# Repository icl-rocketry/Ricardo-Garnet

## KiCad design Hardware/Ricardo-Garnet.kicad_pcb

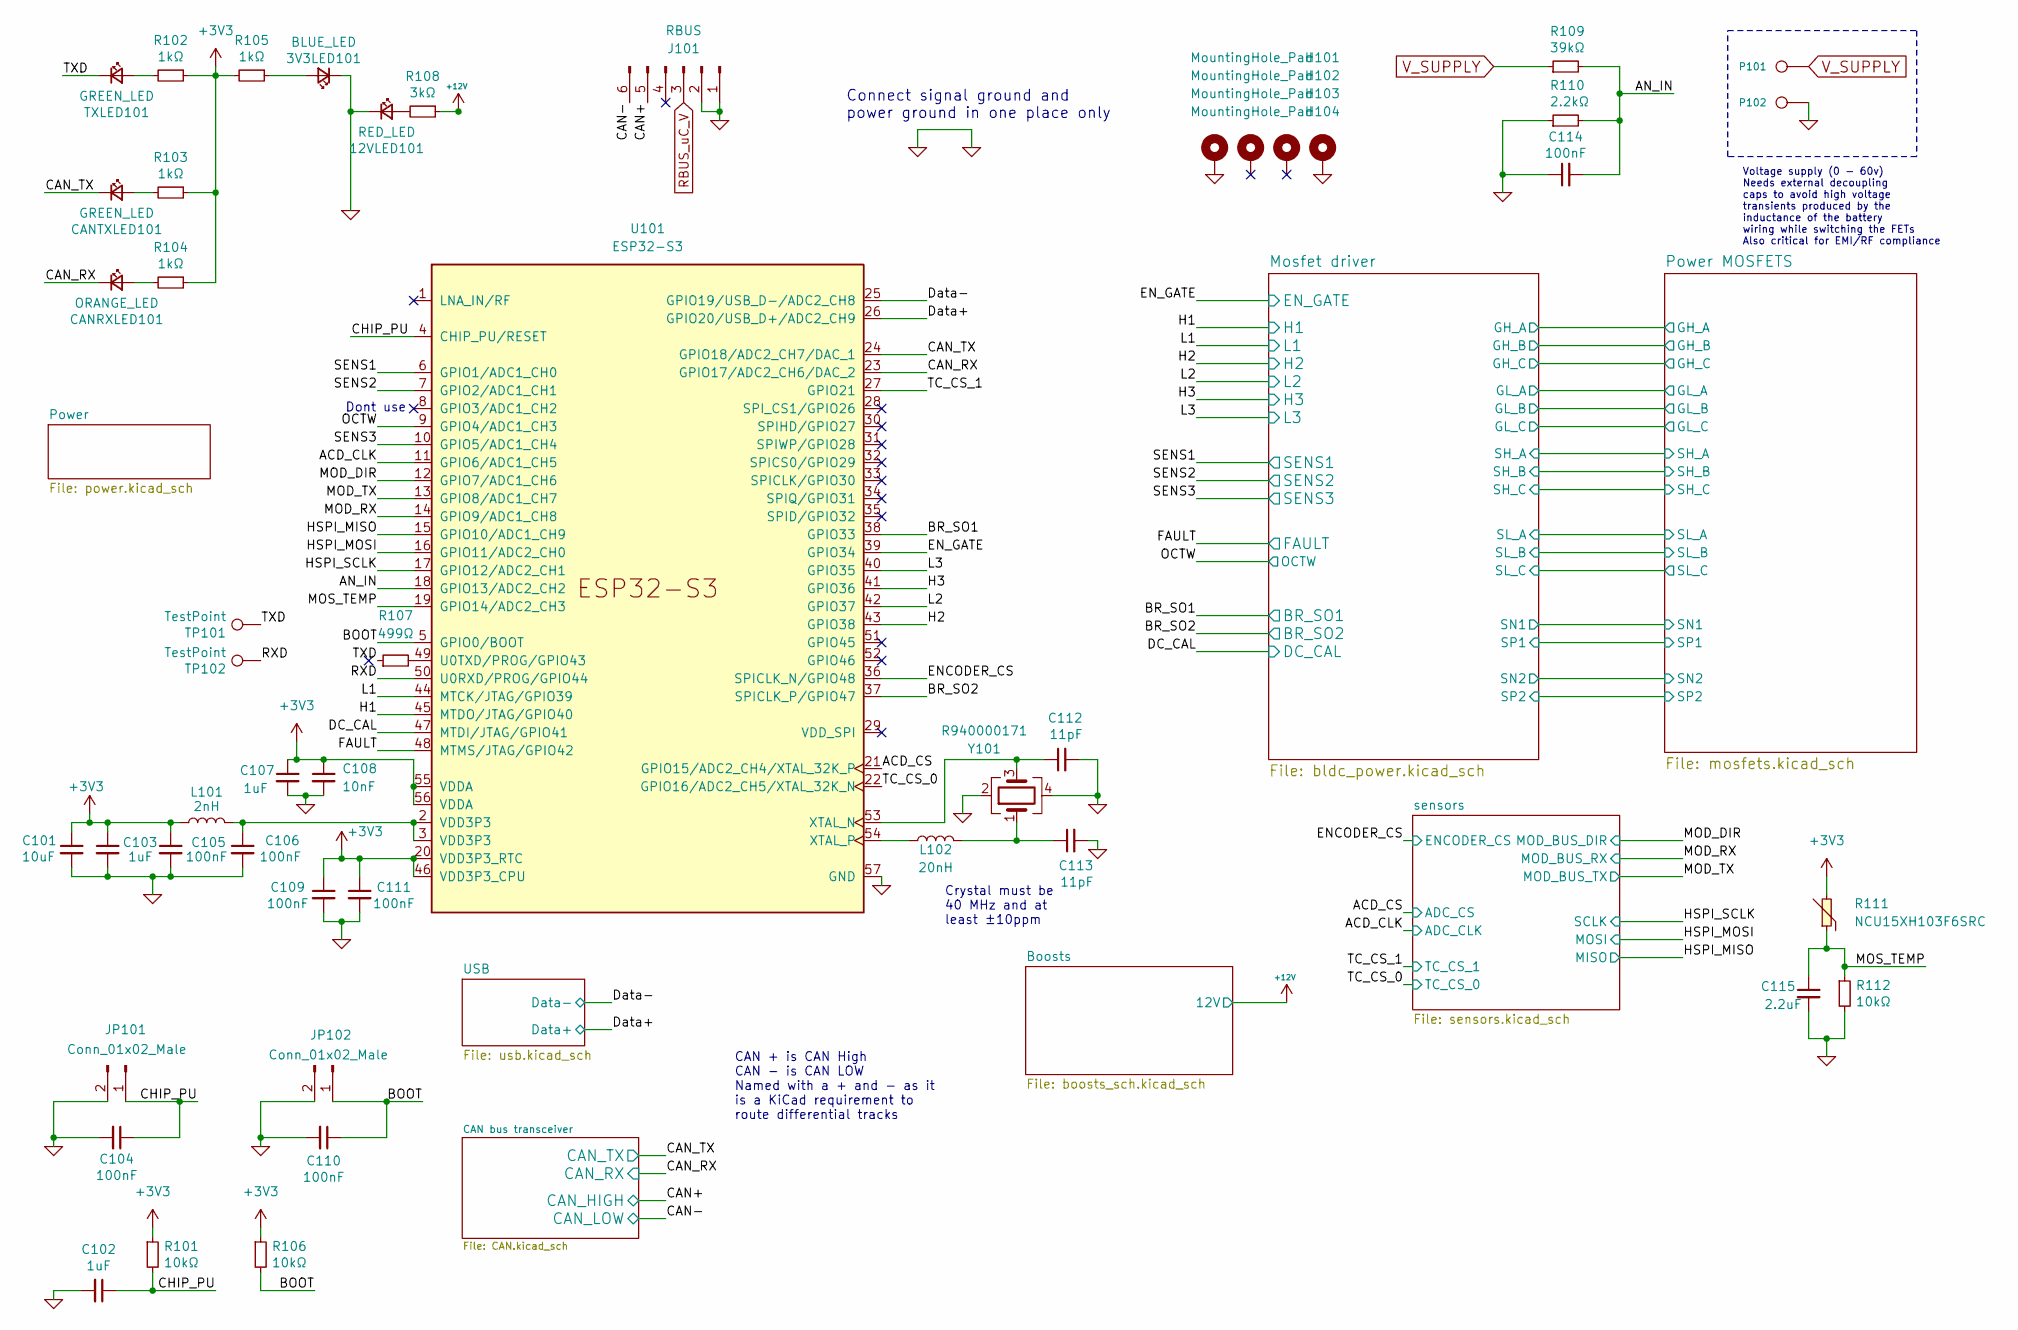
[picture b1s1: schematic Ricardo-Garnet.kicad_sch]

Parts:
3V3LED101: BLUE_LED; LED_0402_1005Metric
12VLED101: RED_LED; LED_0402_1005Metric
C101: 10uF; C_0603_1608Metric
C102, C103, C107: 1uF; C_0402_1005Metric
C104, C105, C106, C109, C110, C111, C114: 100nF; C_0402_1005Metric
C108: 10nF; C_0402_1005Metric
C112, C113: 11pF; C_0402_1005Metric
C115: 2.2uF; C_0402_1005Metric
CANRXLED101: ORANGE_LED; LED_0402_1005Metric
CANTXLED101: GREEN_LED; LED_0402_1005Metric
H101, H102, H103, H104: MountingHole_Pad; MountingHole_3.2mm_M3_DIN965_Pad
J101: RBUS; Molex_Mini-Fit_Jr_5569-06A2_2x03_P4.20mm_Horizontal
JP101, JP102: Conn_01x02_Male; PinHeader_1x02_P2.54mm_Vertical
L101: 2nH; L_0402_1005Metric
L102: 20nH; L_0402_1005Metric
P101: IN+; 1PAD_4x5mm
P102: IN-; 1PAD_4x5mm
R101, R106, R112: 10kΩ; R_0402_1005Metric
R102, R103, R104, R105: 1kΩ; R_0402_1005Metric
R107: 499Ω; R_0402_1005Metric
R108: 3kΩ; R_0402_1005Metric
R109: 39kΩ; R_0402_1005Metric
R110: 2.2kΩ; R_0402_1005Metric
R111: NCU15XH103F6SRC; R0402; MPN NCU15XH103F6SRC; LCSC Part C333993
TP101, TP102: TestPoint; TestPoint_Pad_D1.0mm
TXLED101: GREEN_LED; LED_0402_1005Metric
U101: ESP32-S3; QFN40P700X700X90-57N
Y101: R940000171; Crystal_SMD_2016-4Pin_2.0x1.6mm

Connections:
+3V3: C101.1, C103.1, C105.1, C107.1, C108.1, C109.1, C111.1, L101.1, R101.1, R102.1, R103.1, R104.1, R105.2, R106.1, R111.2, U101.20 (VDD3P3_RTC), U101.46 (VDD3P3_CPU), U101.55 (VDDA), U101.56 (VDDA); also elsewhere on the board
+12V: R108.1; also elsewhere on the board
/ACD_CLK: U101.11 (GPIO6/ADC1_CH5); also elsewhere on the board
/ACD_CS: U101.21 (GPIO15/ADC2_CH4/XTAL_32K_P); also elsewhere on the board
/AN_IN: C114.2, R109.2, R110.2, U101.18 (GPIO13/ADC2_CH2)
/BOOT: C110.1, JP102.1, R106.2, U101.5 (GPIO0/BOOT)
/BR_SO1: U101.38 (GPIO33); also elsewhere on the board
/BR_SO2: U101.37 (SPICLK_P/GPIO47); also elsewhere on the board
/CAN+: J101.5; also elsewhere on the board
/CAN-: J101.6; also elsewhere on the board
/CAN_RX: CANRXLED101.1 (K), U101.23 (GPIO17/ADC2_CH6/DAC_2); also elsewhere on the board
/CAN_TX: CANTXLED101.1 (K), U101.24 (GPIO18/ADC2_CH7/DAC_1); also elsewhere on the board
/CHIP_PU: C102.1, C104.1, JP101.1, R101.2, U101.4 (CHIP_PU/RESET)
/DC_CAL: U101.47 (MTDI/JTAG/GPIO41); also elsewhere on the board
/Data+: U101.26 (GPIO20/USB_D+/ADC2_CH9); also elsewhere on the board
/Data-: U101.25 (GPIO19/USB_D-/ADC2_CH8); also elsewhere on the board
/ENCODER_CS: U101.36 (SPICLK_N/GPIO48); also elsewhere on the board
/EN_GATE: U101.39 (GPIO34); also elsewhere on the board
/FAULT: U101.48 (MTMS/JTAG/GPIO42); also elsewhere on the board
/H1: U101.45 (MTDO/JTAG/GPIO40); also elsewhere on the board
/H2: U101.43 (GPIO38); also elsewhere on the board
/H3: U101.41 (GPIO36); also elsewhere on the board
/HSPI_MISO: U101.15 (GPIO10/ADC1_CH9); also elsewhere on the board
/HSPI_MOSI: U101.16 (GPIO11/ADC2_CH0); also elsewhere on the board
/HSPI_SCLK: U101.17 (GPIO12/ADC2_CH1); also elsewhere on the board
/L1: U101.44 (MTCK/JTAG/GPIO39); also elsewhere on the board
/L2: U101.42 (GPIO37); also elsewhere on the board
/L3: U101.40 (GPIO35); also elsewhere on the board
/MOD_DIR: U101.12 (GPIO7/ADC1_CH6); also elsewhere on the board
/MOD_RX: U101.14 (GPIO9/ADC1_CH8); also elsewhere on the board
/MOD_TX: U101.13 (GPIO8/ADC1_CH7); also elsewhere on the board
/MOS_TEMP: C115.1, R111.1, R112.1, U101.19 (GPIO14/ADC2_CH3)
/OCTW: U101.9 (GPIO4/ADC1_CH3); also elsewhere on the board
/RXD: TP102.1, U101.50 (U0RXD/PROG/GPIO44)
/SENS1: U101.6 (GPIO1/ADC1_CH0); also elsewhere on the board
/SENS2: U101.7 (GPIO2/ADC1_CH1); also elsewhere on the board
/SENS3: U101.10 (GPIO5/ADC1_CH4); also elsewhere on the board
/TC_CS_0: U101.22 (GPIO16/ADC2_CH5/XTAL_32K_N); also elsewhere on the board
/TC_CS_1: U101.27 (GPIO21); also elsewhere on the board
/TXD: R107.1, TP101.1, TXLED101.1 (K)
GND: 3V3LED101.1 (K), 12VLED101.1 (K), C101.2, C102.2, C103.2, C104.2, C105.2, C106.2, C107.2, C108.2, C109.2, C110.2, C111.2, C112.2, C113.2, C114.1, C115.2, H101.1, H104.1, J101.1, J101.2, JP101.2, JP102.2, P102.1, R110.1, R112.2, U101.57 (GND), Y101.2, Y101.4; also elsewhere on the board
unnamed: 3V3LED101.2 (A), R105.1
unnamed: 12VLED101.2 (A), R108.2
unnamed: C106.1, L101.2, U101.2 (VDD3P3), U101.3 (VDD3P3)
unnamed: C113.1, L102.2, Y101.1
unnamed: CANRXLED101.2 (A), R104.2
unnamed: CANTXLED101.2 (A), R103.2
unnamed: R102.2, TXLED101.2 (A)
unnamed: R107.2, U101.49 (U0TXD/PROG/GPIO43)
unnamed: C112.1, U101.53 (XTAL_N), Y101.3
unnamed: L102.1, U101.54 (XTAL_P)
RBUS_uC_V: J101.3; also elsewhere on the board
V_SUPPLY: P101.1, R109.1; also elsewhere on the board

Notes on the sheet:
Connect signal ground and power ground in one place only
Dont use
Voltage supply (0 - 60v) Needs external decoupling caps to avoid high voltage transients produced by the inductance of the battery wiring while switching the FETs Also critical for EMI/RF compliance
CAN + is CAN High CAN - is CAN LOW Named with a + and - as it is a KiCad requirement to route differential tracks
Crystal must be 40 MHz and at least ±10ppm

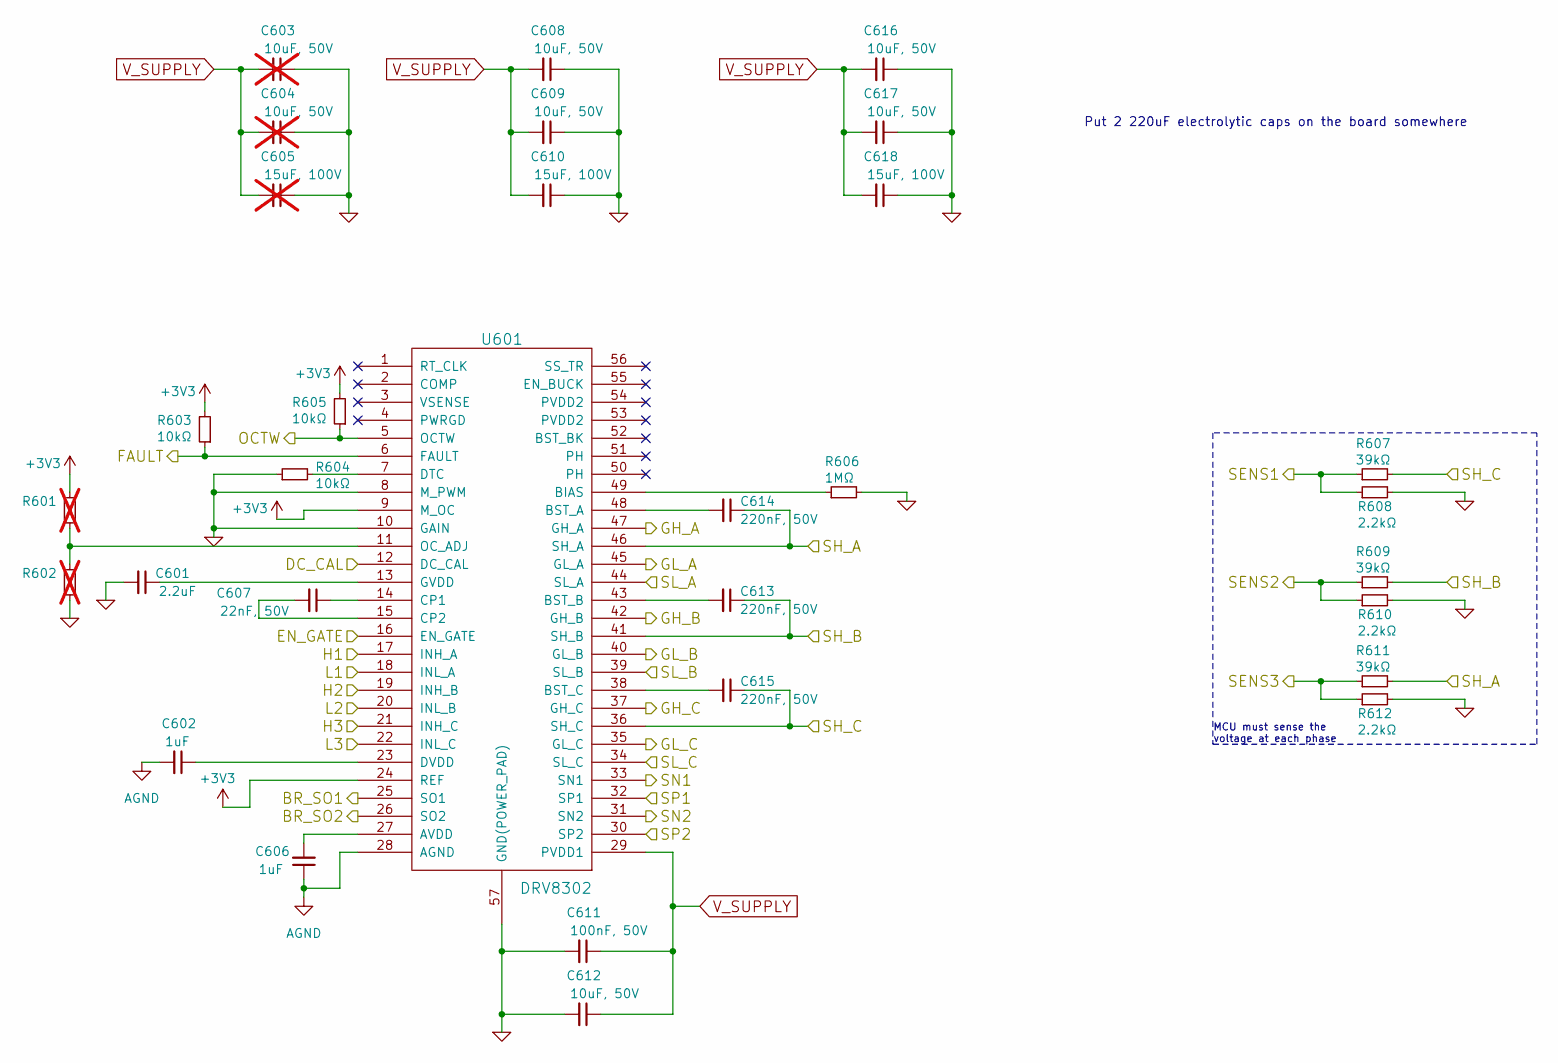
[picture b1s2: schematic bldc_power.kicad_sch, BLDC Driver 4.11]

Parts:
C601: 2.2uF; C_0402_1005Metric
C602, C606: 1uF; C_0402_1005Metric
C603, C604: 10uF, 50V; C_1206_3216Metric; not fitted
C605: 15uF, 100V; C_2220_5750Metric; not fitted
C607: 22nF, 50V; C_0402_1005Metric
C608, C609, C612, C616, C617: 10uF, 50V; C_1206_3216Metric
C610, C618: 15uF, 100V; C_2220_5750Metric
C611: 100nF, 50V; C_0603_1608Metric
C613, C614, C615: 220nF, 50V; C_0402_1005Metric
R601, R602: R_0402_1005Metric; not fitted
R603, R604, R605: 10kΩ; R_0402_1005Metric
R606: 1MΩ; R_0402_1005Metric
R607, R609, R611: 39kΩ; R_0402_1005Metric
R608, R610, R612: 2.2kΩ; R_0402_1005Metric
U601: DRV8302; TSSOP-56-PP

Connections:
+3V3: R601.2, R603.2, R605.2, U601.9 (M_OC), U601.24 (REF); also elsewhere on the board
/BR_SO1: U601.25 (SO1); also elsewhere on the board
/BR_SO2: U601.26 (SO2); also elsewhere on the board
/DC_CAL: U601.12 (DC_CAL); also elsewhere on the board
/EN_GATE: U601.16 (EN_GATE); also elsewhere on the board
/FAULT: R603.1, U601.6 (FAULT); also elsewhere on the board
/H1: U601.17 (INH_A); also elsewhere on the board
/H2: U601.19 (INH_B); also elsewhere on the board
/H3: U601.21 (INH_C); also elsewhere on the board
/L1: U601.18 (INL_A); also elsewhere on the board
/L2: U601.20 (INL_B); also elsewhere on the board
/L3: U601.22 (INL_C); also elsewhere on the board
/Mosfet driver/GH_A: U601.47 (GH_A); also elsewhere on the board
/Mosfet driver/GH_B: U601.42 (GH_B); also elsewhere on the board
/Mosfet driver/GH_C: U601.37 (GH_C); also elsewhere on the board
/Mosfet driver/GL_A: U601.45 (GL_A); also elsewhere on the board
/Mosfet driver/GL_B: U601.40 (GL_B); also elsewhere on the board
/Mosfet driver/GL_C: U601.35 (GL_C); also elsewhere on the board
/Mosfet driver/SH_A: C614.1, R611.2, U601.46 (SH_A); also elsewhere on the board
/Mosfet driver/SH_B: C613.1, R609.2, U601.41 (SH_B); also elsewhere on the board
/Mosfet driver/SH_C: C615.1, R607.2, U601.36 (SH_C); also elsewhere on the board
/Mosfet driver/SN1: U601.33 (SN1); also elsewhere on the board
/Mosfet driver/SN2: U601.31 (SN2); also elsewhere on the board
/Mosfet driver/SP1: U601.32 (SP1); also elsewhere on the board
/Mosfet driver/SP2: U601.30 (SP2); also elsewhere on the board
/OCTW: R605.1, U601.5 (OCTW); also elsewhere on the board
/Power MOSFETS/GND before shunt1: U601.44 (SL_A); also elsewhere on the board
/Power MOSFETS/GND before shunt2: U601.34 (SL_C); also elsewhere on the board
/SENS1: R607.1, R608.1; also elsewhere on the board
/SENS2: R609.1, R610.1; also elsewhere on the board
/SENS3: R611.1, R612.1; also elsewhere on the board
AGND: C602.2, C606.1, U601.28 (AGND)
GND: C601.2, C603.1, C604.1, C605.1, C608.1, C609.1, C610.1, C611.2, C612.2, C616.1, C617.1, C618.1, R602.1, R604.1, R606.2, R608.2, R610.2, R612.2, U601.8 (M_PWM), U601.10 (GAIN), U601.39 (SL_B), U601.57 (GND(POWER_PAD)); also elsewhere on the board
unnamed: C606.2, U601.27 (AVDD)
unnamed: R606.1, U601.49 (BIAS)
unnamed: C614.2, U601.48 (BST_A)
unnamed: C613.2, U601.43 (BST_B)
unnamed: C615.2, U601.38 (BST_C)
unnamed: C607.1, U601.14 (CP1)
unnamed: C607.2, U601.15 (CP2)
unnamed: R604.2, U601.7 (DTC)
unnamed: C602.1, U601.23 (DVDD)
unnamed: C601.1, U601.13 (GVDD)
unnamed: R601.1, R602.2, U601.11 (OC_ADJ)
V_SUPPLY: C603.2, C604.2, C605.2, C608.2, C609.2, C610.2, C611.1, C612.1, C616.2, C617.2, C618.2, U601.29 (PVDD1); also elsewhere on the board

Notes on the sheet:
Put 2 220uF electrolytic caps on the board somewhere
MCU must sense the voltage at each phase

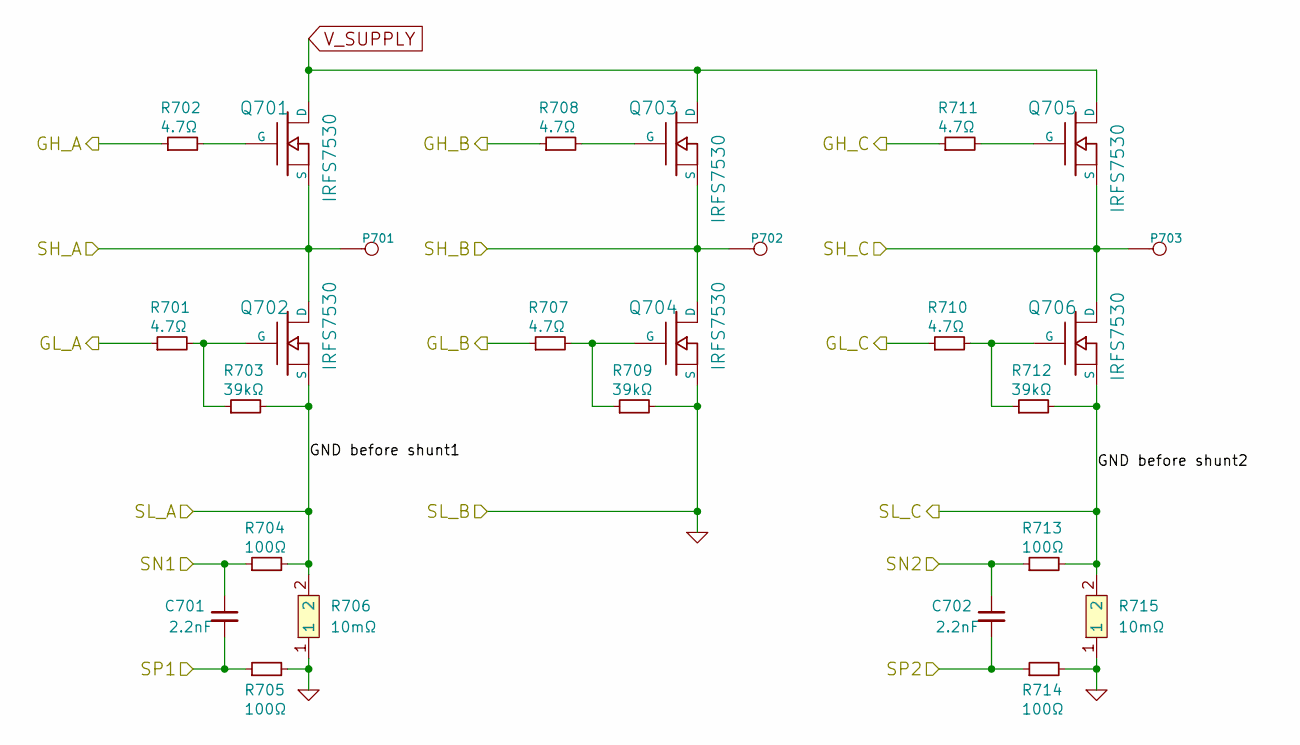
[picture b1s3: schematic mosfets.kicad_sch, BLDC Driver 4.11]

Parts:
C701, C702: 2.2nF; C_0402_1005Metric
P701: MOTOR3; 1PAD_4x5mm
P702: MOTOR2; 1PAD_4x5mm
P703: MOTOR1; 1PAD_4x5mm
Q701, Q702, Q703, Q704, Q705, Q706: IRFS7530; D2PAK-7-GDS
R701, R702, R707, R708, R710, R711: 4.7Ω; R_0603_1608Metric
R703, R709, R712: 39kΩ; R_0402_1005Metric
R704, R705, R713, R714: 100Ω; R_0402_1005Metric
R706, R715: 10mΩ; RES-SMD_L7.1-W4.6_HOXLR2818; MPN HoRCG28185R010F4T; LCSC Part C53115042

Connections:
/Mosfet driver/GH_A: R702.1; also elsewhere on the board
/Mosfet driver/GH_B: R708.1; also elsewhere on the board
/Mosfet driver/GH_C: R711.1; also elsewhere on the board
/Mosfet driver/GL_A: R701.1; also elsewhere on the board
/Mosfet driver/GL_B: R707.1; also elsewhere on the board
/Mosfet driver/GL_C: R710.1; also elsewhere on the board
/Mosfet driver/SH_A: P701.1, Q701.S, Q702.D; also elsewhere on the board
/Mosfet driver/SH_B: P702.1, Q703.S, Q704.D; also elsewhere on the board
/Mosfet driver/SH_C: P703.1, Q705.S, Q706.D; also elsewhere on the board
/Mosfet driver/SN1: C701.1, R704.1; also elsewhere on the board
/Mosfet driver/SN2: C702.1, R713.1; also elsewhere on the board
/Mosfet driver/SP1: C701.2, R705.1; also elsewhere on the board
/Mosfet driver/SP2: C702.2, R714.1; also elsewhere on the board
/Power MOSFETS/GND before shunt1: Q702.S, R703.2, R704.2, R706.2; also elsewhere on the board
/Power MOSFETS/GND before shunt2: Q706.S, R712.2, R713.2, R715.2; also elsewhere on the board
GND: Q704.S, R705.2, R706.1, R709.2, R714.2, R715.1; also elsewhere on the board
unnamed: Q701.G, R702.2
unnamed: Q702.G, R701.2, R703.1
unnamed: Q703.G, R708.2
unnamed: Q704.G, R707.2, R709.1
unnamed: Q705.G, R711.2
unnamed: Q706.G, R710.2, R712.1
V_SUPPLY: Q701.D, Q703.D, Q705.D; also elsewhere on the board

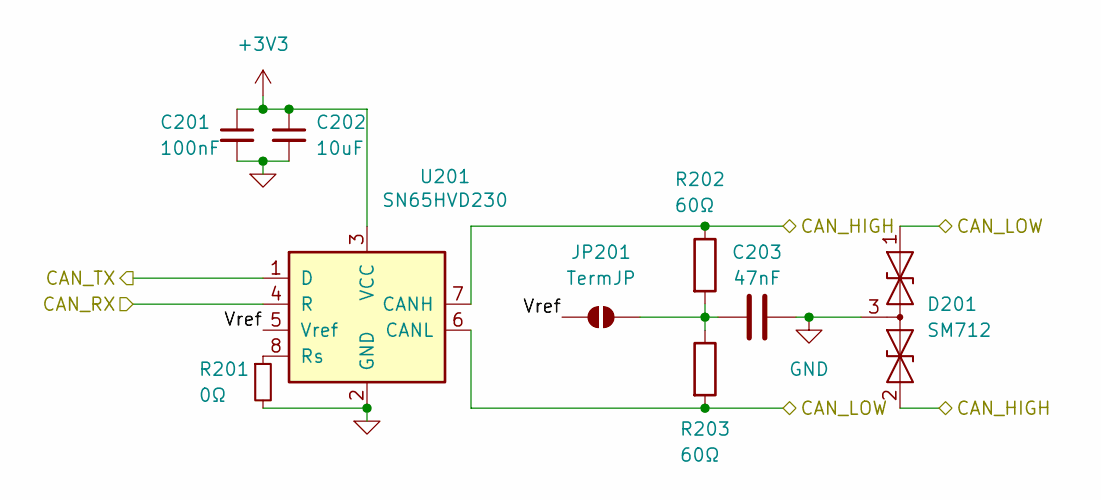
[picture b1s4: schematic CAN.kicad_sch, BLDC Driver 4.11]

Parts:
C201: 100nF; C_0402_1005Metric
C202: 10uF; C_0603_1608Metric
C203: 47nF; C_0402_1005Metric
D201: SM712; SOT-23
JP201: TermJP; SmallerSolderJP
R201: 0Ω; R_0603_1608Metric
R202, R203: 60Ω; R_0603_1608Metric
U201: SN65HVD230; SOIC-8_3.9x4.9mm_P1.27mm

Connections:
+3V3: C201.1, C202.1, U201.3 (VCC); also elsewhere on the board
/CAN bus transceiver/Vref: JP201.1 (A), U201.5 (Vref)
/CAN+: D201.2 (A2), R202.1, U201.7 (CANH); also elsewhere on the board
/CAN-: D201.1 (A1), R203.2, U201.6 (CANL); also elsewhere on the board
/CAN_RX: U201.4 (R); also elsewhere on the board
/CAN_TX: U201.1 (D); also elsewhere on the board
GND: C201.2, C202.2, C203.2, D201.3 (common), R201.2, U201.2 (GND); also elsewhere on the board
unnamed: C203.1, JP201.2 (B), R202.2, R203.1
unnamed: R201.1, U201.8 (Rs)

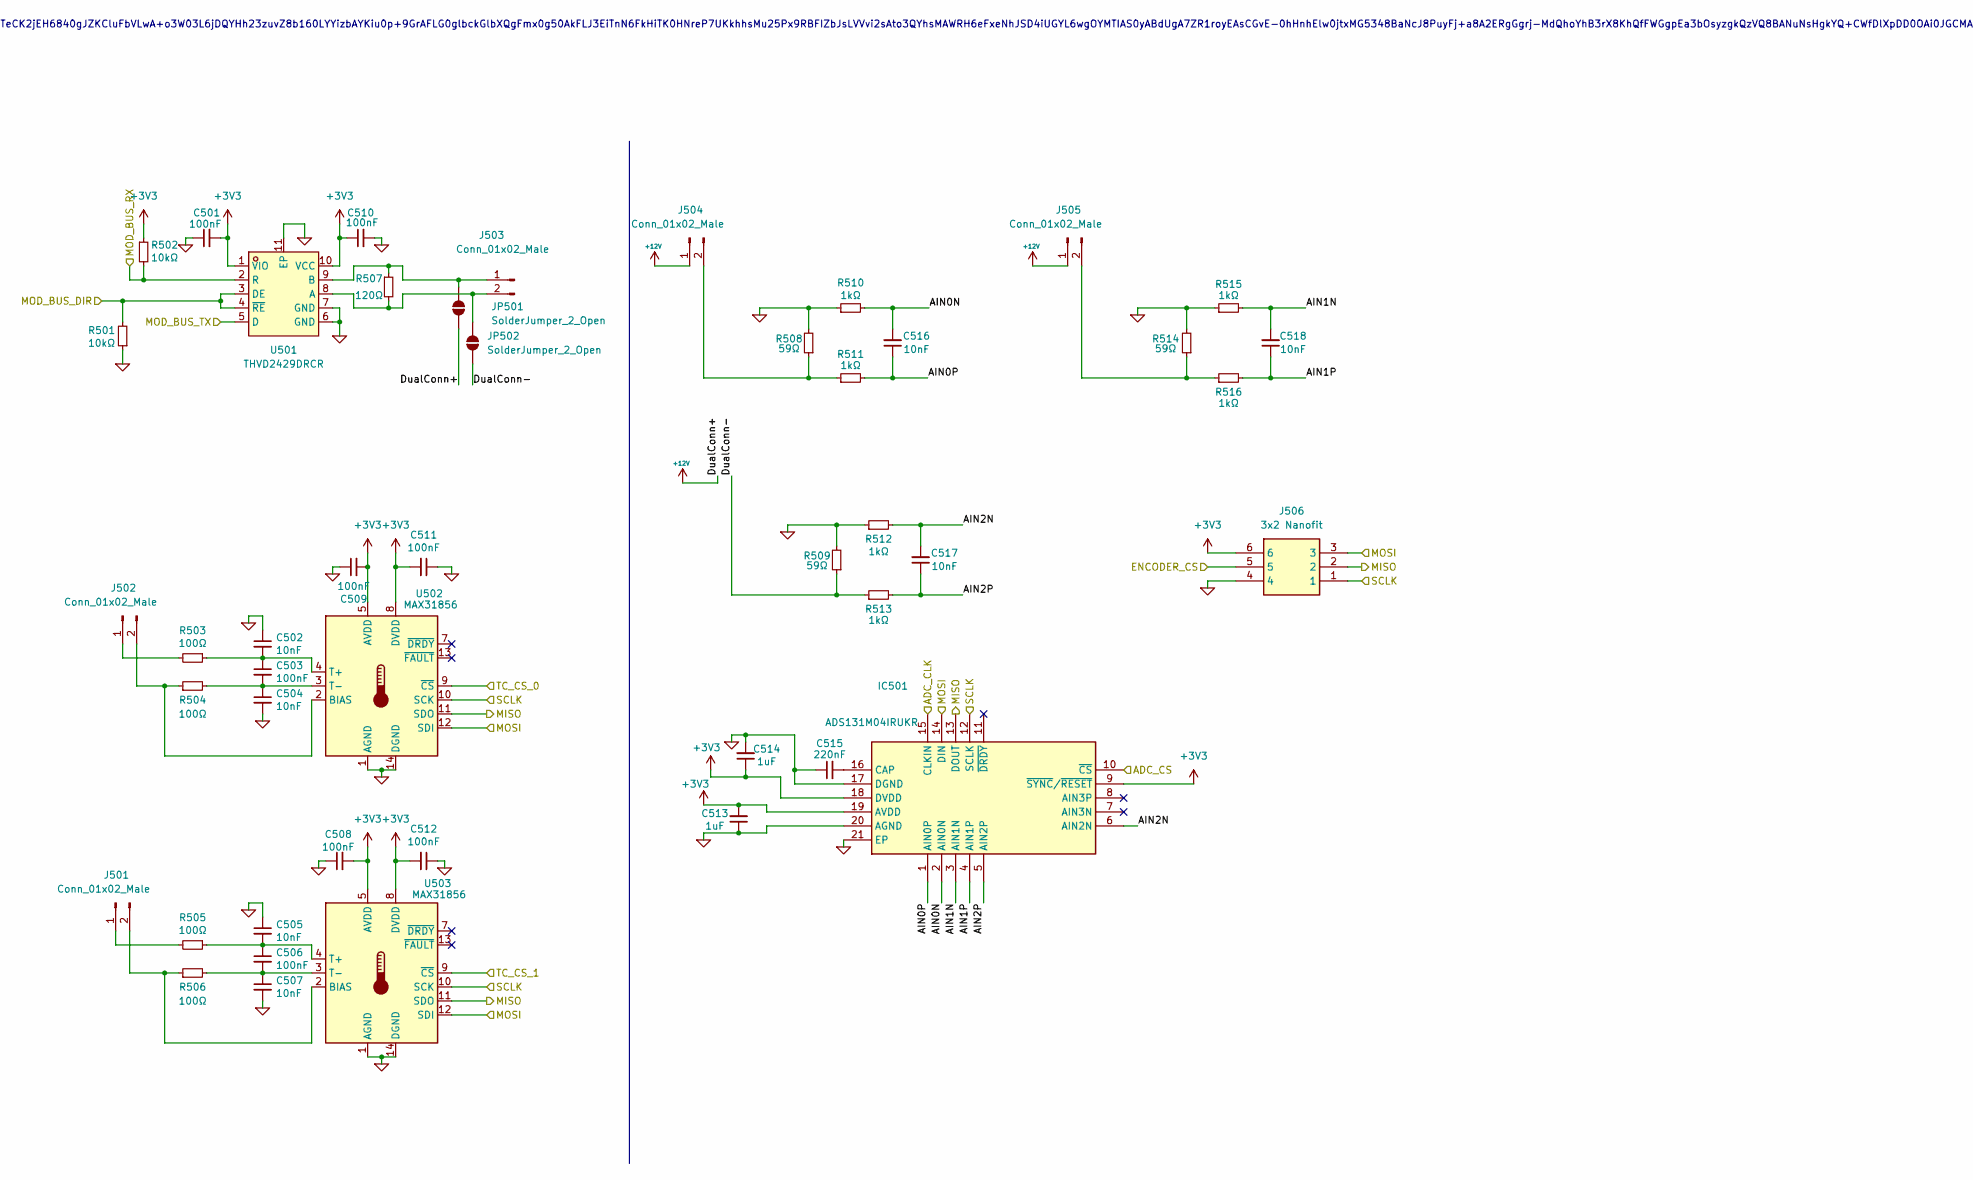
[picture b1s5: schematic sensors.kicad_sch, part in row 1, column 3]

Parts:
C501, C503, C506, C508, C509, C510, C511, C512: 100nF; C_0402_1005Metric
C502, C504, C505, C507, C516, C517, C518: 10nF; C_0402_1005Metric
C513, C514: 1uF; C_0402_1005Metric
C515: 220nF; C_0402_1005Metric
IC501: ADS131M04IRUKR; QFN40P300X300X80-21N-D; Manufacturer_Part_Number ADS131M04IRUKR; Mouser Part Number 595-ADS131M04IRUKR
J501, J502, J503, J504, J505: Conn_01x02_Male; Molex_Nano-Fit_105313-xx02_1x02_P2.50mm_Horizontal
J506: 3x2 Nanofit; Molex_Nano-Fit_105314-xx06_2x03_P2.50mm_Horizontal; Mouser Part Number 538-105314-1206
JP501, JP502: SolderJumper_2_Open; small_2_pad_jumper_open
R501, R502: 10kΩ; R_0402_1005Metric
R503, R504, R505, R506: 100Ω; R_0402_1005Metric
R507: 120Ω; R_0402_1005Metric
R508, R509, R514: 59Ω; R_0402_1005Metric; MPN RT0402BRD0749R9L
R510, R511, R512, R513, R515, R516: 1kΩ; R_0402_1005Metric
U501: THVD2429DRCR; VSON-10_L3.0-W3.0-P0.50-BL-EP_DRC; MPN THVD2429DRCR; LCSC Part C41755914
U502, U503: MAX31856; TSSOP-14_4.4x5mm_P0.65mm

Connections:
+3V3: C501.2, C508.2, C509.2, C510.1, C511.2, C512.2, C513.2, C514.1, IC501.9 (~SYNC/~RESET), IC501.18 (DVDD), IC501.19 (AVDD), J506.6, R502.1, U501.1 (VIO), U501.10 (VCC), U502.5 (AVDD), U502.8 (DVDD), U503.5 (AVDD), U503.8 (DVDD); also elsewhere on the board
+12V: J504.1, J505.1, JP501.1 (A); also elsewhere on the board
/ACD_CLK: IC501.15 (CLKIN); also elsewhere on the board
/ACD_CS: IC501.10 (~CS); also elsewhere on the board
/ENCODER_CS: J506.5; also elsewhere on the board
/HSPI_MISO: IC501.13 (DOUT), J506.2, U502.11 (SDO), U503.11 (SDO); also elsewhere on the board
/HSPI_MOSI: IC501.14 (DIN), J506.3, U502.12 (SDI), U503.12 (SDI); also elsewhere on the board
/HSPI_SCLK: IC501.12 (SCLK), J506.1, U502.10 (SCK), U503.10 (SCK); also elsewhere on the board
/MOD_DIR: R501.2, U501.3 (DE), U501.4 (~RE); also elsewhere on the board
/MOD_RX: R502.2, U501.2 (R); also elsewhere on the board
/MOD_TX: U501.5 (D); also elsewhere on the board
/TC_CS_0: U502.9 (~CS); also elsewhere on the board
/TC_CS_1: U503.9 (~CS); also elsewhere on the board
/sensors/AIN0N: C516.2, IC501.2 (AIN0N), R510.2
/sensors/AIN0P: C516.1, IC501.1 (AIN0P), R511.2
/sensors/AIN1N: C518.2, IC501.3 (AIN1N), R515.2
/sensors/AIN1P: C518.1, IC501.4 (AIN1P), R516.2
/sensors/AIN2N: C517.2, IC501.6 (AIN2N), R512.2
/sensors/AIN2P: C517.1, IC501.5 (AIN2P), R513.2
/sensors/DualConn-: JP502.1 (A), R509.1, R513.1
GND: C501.1, C502.1, C504.2, C505.1, C507.2, C508.1, C509.1, C510.2, C511.1, C512.1, C513.1, C514.2, C515.1, IC501.17 (DGND), IC501.20 (AGND), IC501.21 (EP), J506.4, R501.1, R508.2, R509.2, R510.1, R512.1, R514.2, R515.1, U501.6 (GND), U501.7 (GND), U501.11 (EP), U502.1 (AGND), U502.14 (DGND), U503.1 (AGND), U503.14 (DGND); also elsewhere on the board
unnamed: C515.2, IC501.16 (CAP)
unnamed: J501.1, R505.2
unnamed: J501.2, R506.1, U503.2 (BIAS)
unnamed: J502.1, R503.2
unnamed: J502.2, R504.1, U502.2 (BIAS)
unnamed: J503.1, JP501.2 (B), R507.1, U501.9 (B)
unnamed: J503.2, JP502.2 (B), R507.2, U501.8 (A)
unnamed: J504.2, R508.1, R511.1
unnamed: J505.2, R514.1, R516.1
unnamed: C502.2, C503.1, R503.1, U502.4 (T+)
unnamed: C503.2, C504.1, R504.2, U502.3 (T-)
unnamed: C505.2, C506.1, R505.1, U503.4 (T+)
unnamed: C506.2, C507.1, R506.2, U503.3 (T-)

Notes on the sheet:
https://www.falstad.com/circuit/circuitjs.html?ctz=CQAgjCAMB0l3BWcMBMcUHYMGZIA4UA2ATmIxAUgpABZsKBTAWjDACgB3EQvPcFPgmIp+fSJ268QKGlSEiZVcQGMKw0WoWza4ZnxbQwebNhoyMNQnDCUaUWJAjiuJwtzuuN4gE6aNNPCowAShkODYAZWkMBXxorSVwEAAzAEMAGwBnBlCUCWwEBOkpRSh8wultOiKfWjgQT2w0Buw3INlwrlLu7U9xAAdJPlKePmC+ekSweBm2ACUNQI1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

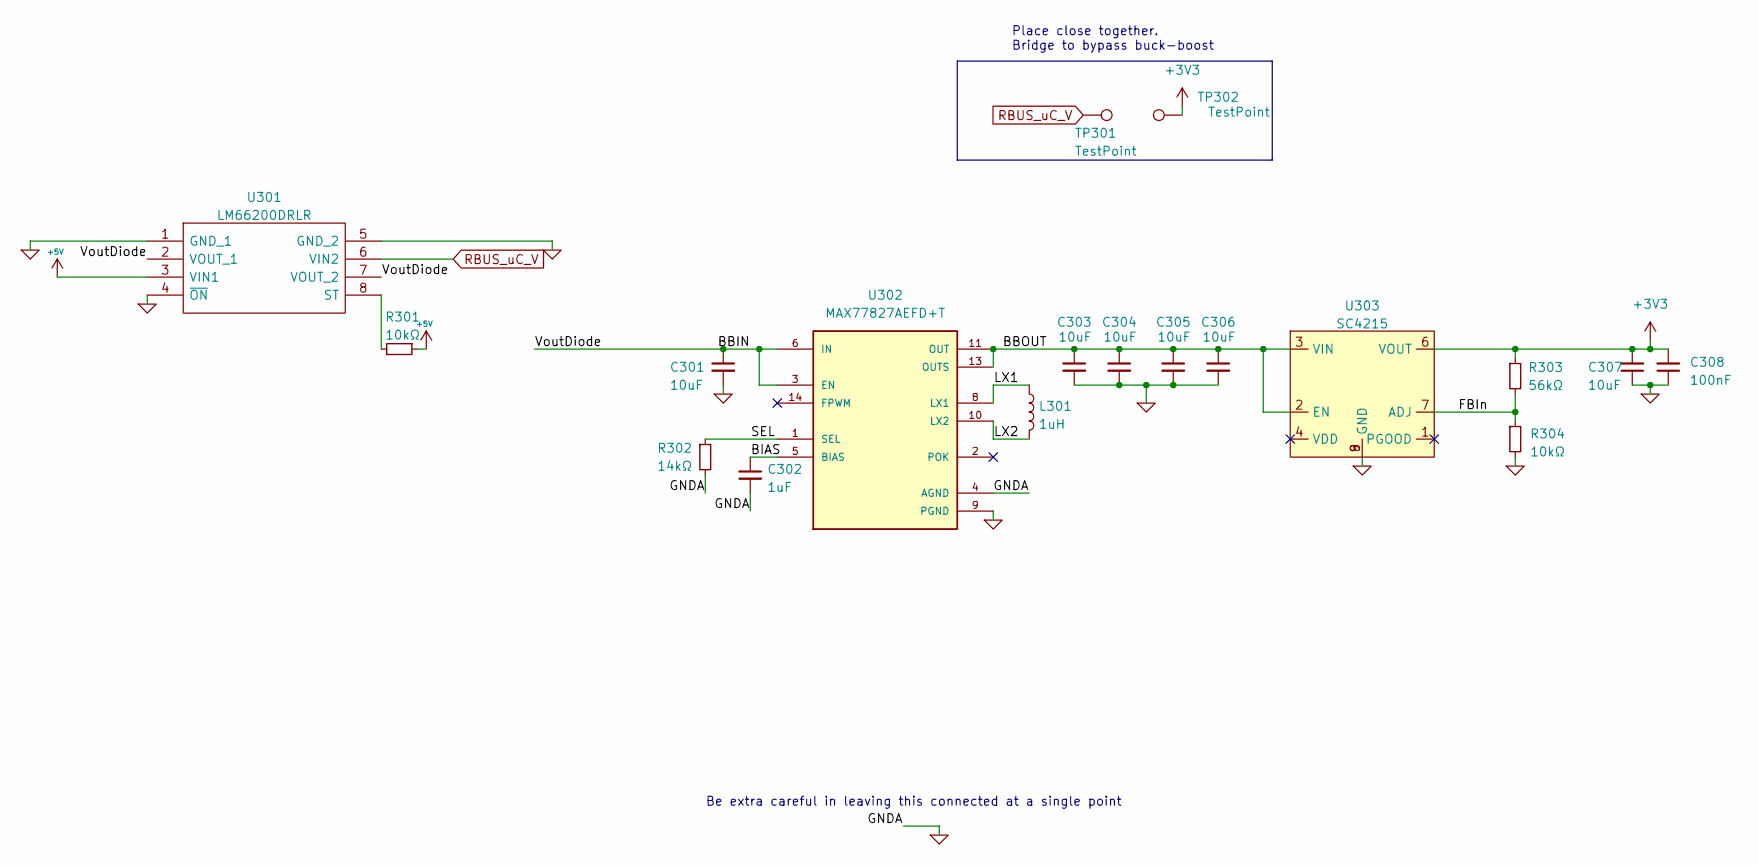
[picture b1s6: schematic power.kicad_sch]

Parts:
C301, C303, C304, C305, C306: 10uF; C_0603_1608Metric
C302: 1uF; C_0402_1005Metric
C307: 10uF; C_0402_1005Metric
C308: 100nF; C_0402_1005Metric
L301: 1uH; L_0805_2012Metric
R301, R304: 10kΩ; R_0402_1005Metric
R302: 14kΩ; R_0402_1005Metric
R303: 56kΩ; R_0402_1005Metric
TP301, TP302: TestPoint; TestPoint_Pad_D1.5mm
U301: LM66200DRLR; SOTFL50P160X60-8N; Manufacturer_Part_Number LM66200DRLR; Mouser Part Number 595-LM66200DRLR
U302: MAX77827AEFD+T; CONV_MAX77827AEFD+T; PARTREV B
U303: SC4215; SOIC127P599X175-9N

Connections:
+3V3: C307.2, C308.2, R303.1, TP302.1, U303.6 (VOUT); also elsewhere on the board
+5V: R301.1, U301.3 (VIN1); also elsewhere on the board
/Power/BBIN: C301.1, U301.2 (VOUT_1), U301.7 (VOUT_2), U302.3 (EN), U302.6 (IN)
/Power/BBOUT: C303.1, C304.1, C305.1, C306.1, U302.11 (OUT), U302.13 (OUTS), U303.2 (EN), U303.3 (VIN)
/Power/BIAS: C302.1, U302.5 (BIAS)
/Power/FBIn: R303.2, R304.1, U303.7 (ADJ)
/Power/LX1: L301.1, U302.8 (LX1)
/Power/LX2: L301.2, U302.10 (LX2)
/Power/SEL: R302.1, U302.1 (SEL)
GND: C301.2, C302.2, C303.2, C304.2, C305.2, C306.2, C307.1, C308.1, R302.2, R304.2, U301.1 (GND_1), U301.4 (~ON), U301.5 (GND_2), U302.4 (AGND), U302.9 (PGND), U303.8 (GND), U303.9 (GND); also elsewhere on the board
unnamed: R301.2, U301.8 (ST)
RBUS_uC_V: TP301.1, U301.6 (VIN2); also elsewhere on the board

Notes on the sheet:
Be extra careful in leaving this connected at a single point
Place close together. Bridge to bypass buck-boost

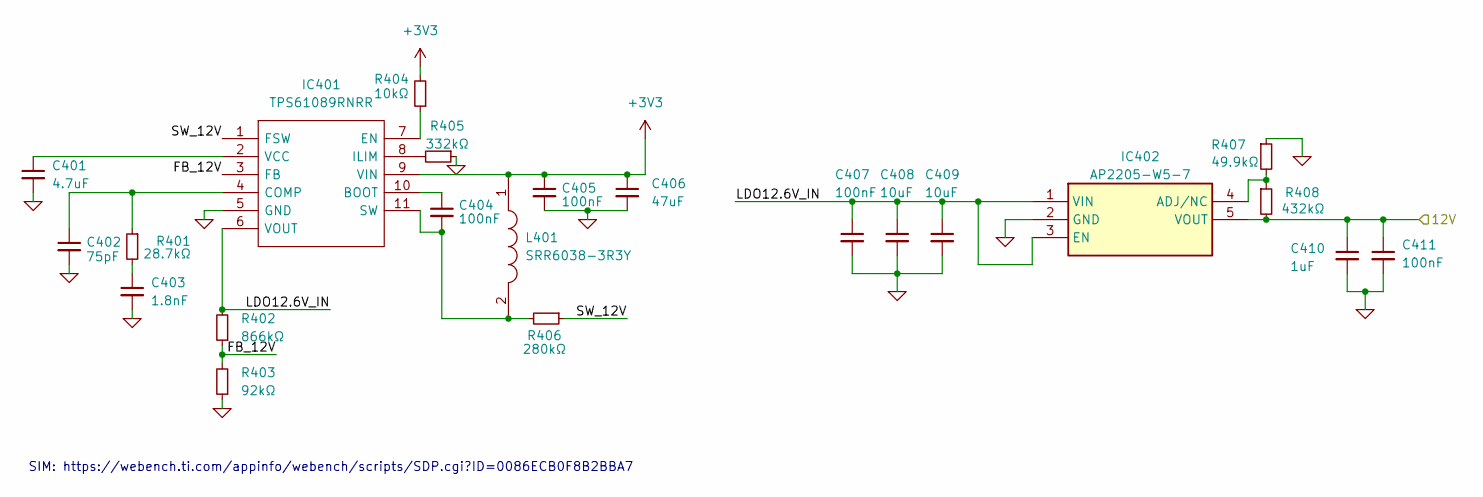
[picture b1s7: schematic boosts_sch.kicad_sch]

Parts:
C401: 4.7uF; C_0603_1608Metric
C402: 75pF; C_0402_1005Metric
C403: 1.8nF; C_0402_1005Metric
C404, C405, C407, C411: 100nF; C_0402_1005Metric
C406: 47uF; C_1206_3216Metric
C408, C409: 10uF; C_0805_2012Metric
C410: 1uF; C_0603_1608Metric
IC401: TPS61089RNRR; IC_TPS61089RNRR; Manufacturer_Part_Number TPS61089RNRR; Mouser Part Number 595-TPS61089RNRR
IC402: AP2205-W5-7; SOT95P282X145-5N; Mouser Part Number 621-AP2205-W5-7
L401: SRR6038-3R3Y; IND_SRP6540-390M; Manufacturer_Part_Number SRR6038-5R0Y; Mouser Part Number 652-SRR6038-5R0Y
R401: 28.7kΩ; R_0402_1005Metric
R402: 866kΩ; R_0402_1005Metric
R403: 92kΩ; R_0402_1005Metric
R404: 10kΩ; R_0402_1005Metric
R405: 332kΩ; R_0402_1005Metric
R406: 280kΩ; R_0402_1005Metric
R407: 49.9kΩ; R_0402_1005Metric
R408: 432kΩ; R_0402_1005Metric

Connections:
+3V3: C405.1, C406.1, IC401.9 (VIN), L401.1, R404.2; also elsewhere on the board
+12V: C410.1, C411.1, IC402.5 (VOUT), R408.2; also elsewhere on the board
/Boosts/FB_12V: IC401.3 (FB), R402.1, R403.2
/Boosts/LDO12.6V_IN: C407.1, C408.1, C409.1, IC401.6 (VOUT), IC402.1 (VIN), IC402.3 (EN), R402.2
/Boosts/SW_12V: IC401.1 (FSW), R406.1
GND: C401.2, C402.2, C403.2, C405.2, C406.2, C407.2, C408.2, C409.2, C410.2, C411.2, IC401.5 (GND), IC402.2 (GND), R403.1, R405.1, R407.1; also elsewhere on the board
unnamed: C403.1, R401.2
unnamed: C404.1, IC401.10 (BOOT)
unnamed: C402.1, IC401.4 (COMP), R401.1
unnamed: IC401.7 (EN), R404.1
unnamed: IC401.8 (ILIM), R405.2
unnamed: C404.2, IC401.11 (SW), L401.2, R406.2
unnamed: C401.1, IC401.2 (VCC)
unnamed: IC402.4 (ADJ/NC), R407.2, R408.1

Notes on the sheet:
SIM: https://webench.ti.com/appinfo/webench/scripts/SDP.cgi?ID=0086ECB0F8B2BBA7

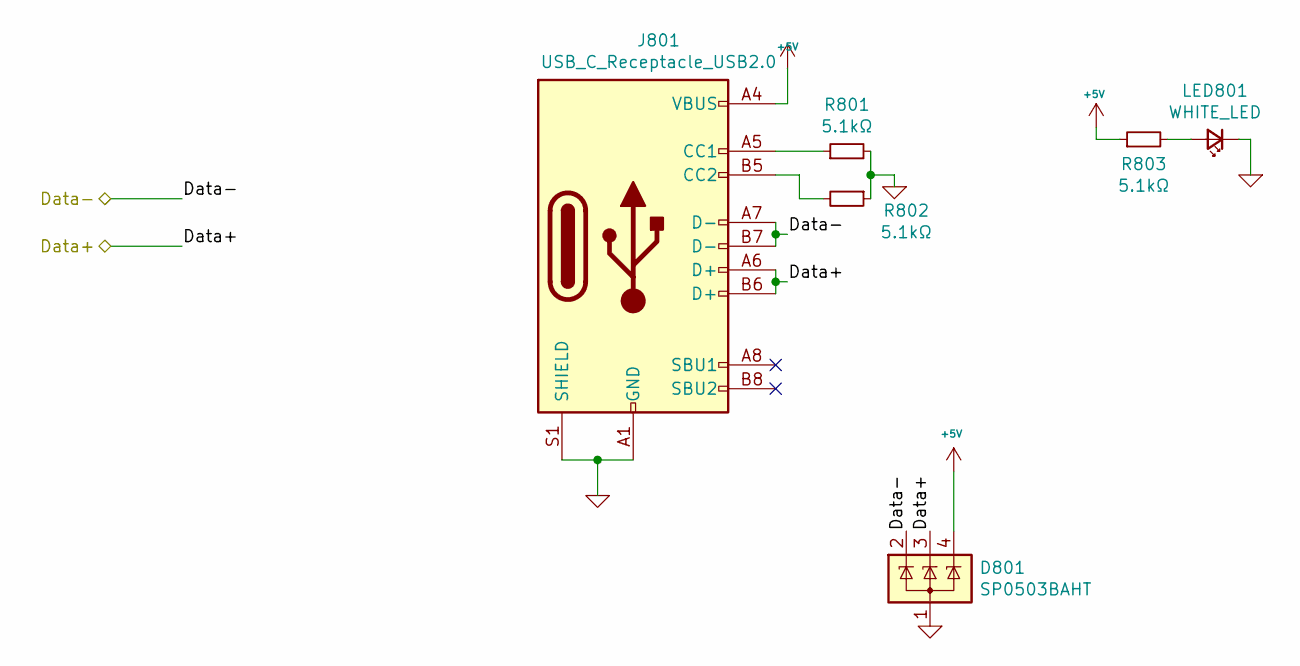
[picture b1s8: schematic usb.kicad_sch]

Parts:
D801: SP0503BAHT; SOT-143
J801: USB_C_Receptacle_USB2.0; USB_C_Receptacle_Palconn_UTC16-G
LED801: WHITE_LED; LED_0402_1005Metric
R801, R802, R803: 5.1kΩ; R_0402_1005Metric

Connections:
+5V: D801.4 (K), J801.A4 (VBUS), J801.A9 (VBUS), J801.B4 (VBUS), J801.B9 (VBUS), R803.1; also elsewhere on the board
/Data+: D801.3 (K), J801.A6 (D+), J801.B6 (D+); also elsewhere on the board
/Data-: D801.2 (K), J801.A7 (D-), J801.B7 (D-); also elsewhere on the board
GND: D801.1 (A), J801.A1 (GND), J801.A12 (GND), J801.B1 (GND), J801.B12 (GND), J801.S1 (SHIELD), LED801.1 (K), R801.2, R802.1; also elsewhere on the board
unnamed: J801.A5 (CC1), R801.1
unnamed: J801.B5 (CC2), R802.2
unnamed: LED801.2 (A), R803.2
